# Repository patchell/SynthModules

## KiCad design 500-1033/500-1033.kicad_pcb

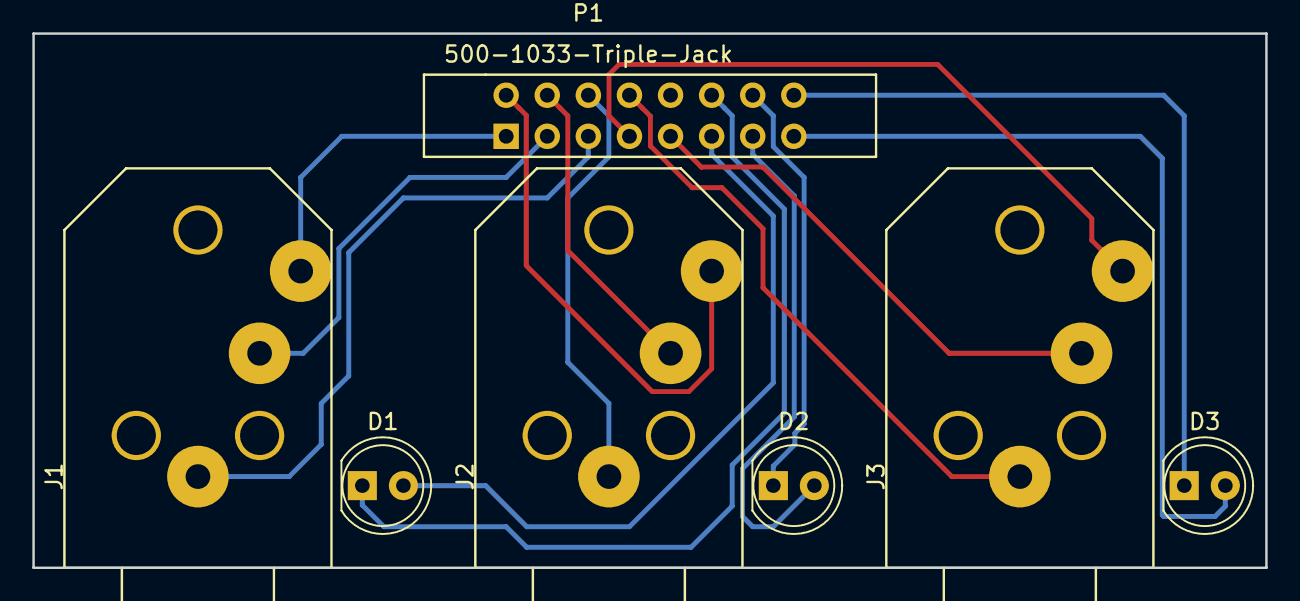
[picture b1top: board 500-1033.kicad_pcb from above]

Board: 2 copper layers, 76.2 x 33.0 mm, 7 parts (0 on the bottom side), 15 nets.

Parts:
D1, D2, D3: LED_ALT; LED_D5.0mm
J1, J2, J3: Phone_Jack_wSw-PCB; PHONE-SC112A
P1: 500-1033-Triple-Jack; IDC8x2_Vert

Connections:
unnamed: D1.1, P1.12
unnamed: D1.2, P1.11
unnamed: D2.1, P1.14
unnamed: D2.2, P1.13
unnamed: D3.1, P1.16
unnamed: D3.2, P1.15
unnamed: J1.1, P1.5
unnamed: J1.2, P1.3
unnamed: J1.3, P1.1
unnamed: J2.1, P1.6
unnamed: J2.2, P1.4
unnamed: J2.3, P1.2
unnamed: J3.1, P1.8
unnamed: J3.2, P1.9
unnamed: J3.3, P1.7

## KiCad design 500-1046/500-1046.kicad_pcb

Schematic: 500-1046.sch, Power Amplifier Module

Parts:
C1: 10uF; Cap-Pol-Rad-0.2_0.1
C2: 100uF; Cap-Pol-Rad-0.2_0.1
C3: 100pF; CAP-GREENIE-0.2
C4, C5, C6, C7: 0.1uF; CAP-GREENIE-0.2
L1: 30uH; AXIAL0.7X0.2
P1: Header_4x1; Header_4Pin_RA_0.1
P2: Header_6x1; TERMINAL-BLOCK-SCREWS
Q1, Q2, Q3, Q6: KSC1845; TO92
Q4, Q5: KSA992; TO92
Q7: MJE340; TO-225
Q8: 2N3904; TO92
Q9: 2N3906; TO92
Q10: TIP142; TO-264
Q11: TIP147; TO-264
R1, R7, R8, R11: 10K; AXIAL0.4
R2, R5: 1.2K; AXIAL0.4
R3, R6: 220; AXIAL0.4
R4: 909; AXIAL0.4
R10, R18: 390; AXIAL0.4
R12, R17, R21, R22: 1K; AXIAL0.4
R13: 15K; AXIAL0.4
R14: 10; AXIAL0.4
R15: 2.2K; AXIAL0.4
R16: 1K; Trimpot-3006
R19, R20: 499; AXIAL0.4
R23, R24: .33; AXIAL0.7X0.2
R25, R26: 10; AXIAL0.7X0.2
U1: LM4041-ADJ; TO92

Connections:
/GND_DIRTY: C4.2, C5.1, P2.2
/GND_H: C6.2, P2.5
/OUT: L1.2, P2.4, R26.2
/V+: C4.1, P2.1, Q10.2, R2.1, R5.1, R12.1, R14.1
/V-: C5.2, P2.6, Q11.2, R4.2, R8.2, R18.2, U1.3 (adj)
GND: C2.2, P1.1, P1.3, P1.4, P2.3, R1.2, R13.1
unnamed: C1.1, Q1.3, R1.1
unnamed: C1.2, P1.2
unnamed: C2.1, R10.2
unnamed: C3.1, Q1.2, Q4.3, R2.2
unnamed: C3.2, C7.1, Q4.2, Q5.2, Q7.2, Q8.3, Q10.1, R15.1
unnamed: C6.1, R25.2
unnamed: C7.2, Q6.2, Q7.1, Q9.3, Q11.1, R17.2
unnamed: L1.1, Q8.1, Q9.1, R11.1, R19.1, R20.2, R23.2, R24.1, R25.1, R26.1
unnamed: Q1.1, R3.1
unnamed: Q2.1, R4.1
unnamed: Q2.2, R3.2, R6.2
unnamed: Q2.3, Q6.3, R7.1, R13.2, U1.2 (cath)
unnamed: Q3.1, R6.1
unnamed: Q3.2, R5.2
unnamed: Q3.3, R10.1, R11.2
unnamed: Q4.1, Q5.3, R12.2
unnamed: Q5.1, R14.2
unnamed: Q6.1, R18.1
unnamed: Q7.3, R16.2
unnamed: Q8.2, R19.2, R21.2
unnamed: Q9.2, R20.1, R22.2
unnamed: Q10.3, R21.1, R23.1
unnamed: Q11.3, R22.1, R24.2
unnamed: R7.2, R8.1, U1.1 (anod)
unnamed: R15.2, R16.1
unnamed: R16.3, R17.1

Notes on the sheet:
L1 Wind 4 Turns of #22 Magnet Wire on an Amidon ft-50-j Torrid Core

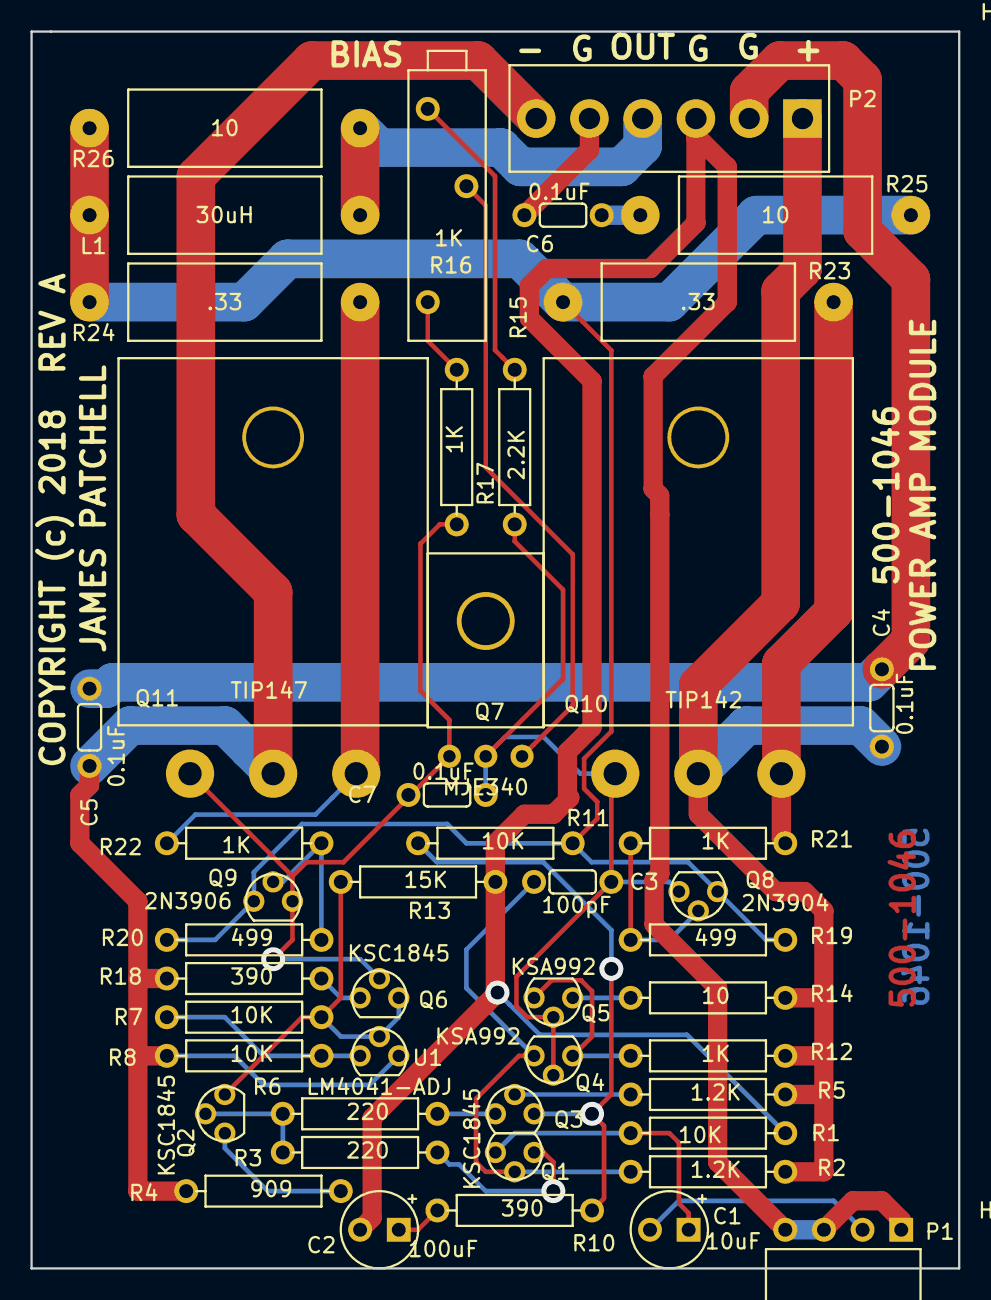
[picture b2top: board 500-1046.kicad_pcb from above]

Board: 2 copper layers, 61.0 x 81.3 mm, 47 parts (0 on the bottom side), 32 nets.

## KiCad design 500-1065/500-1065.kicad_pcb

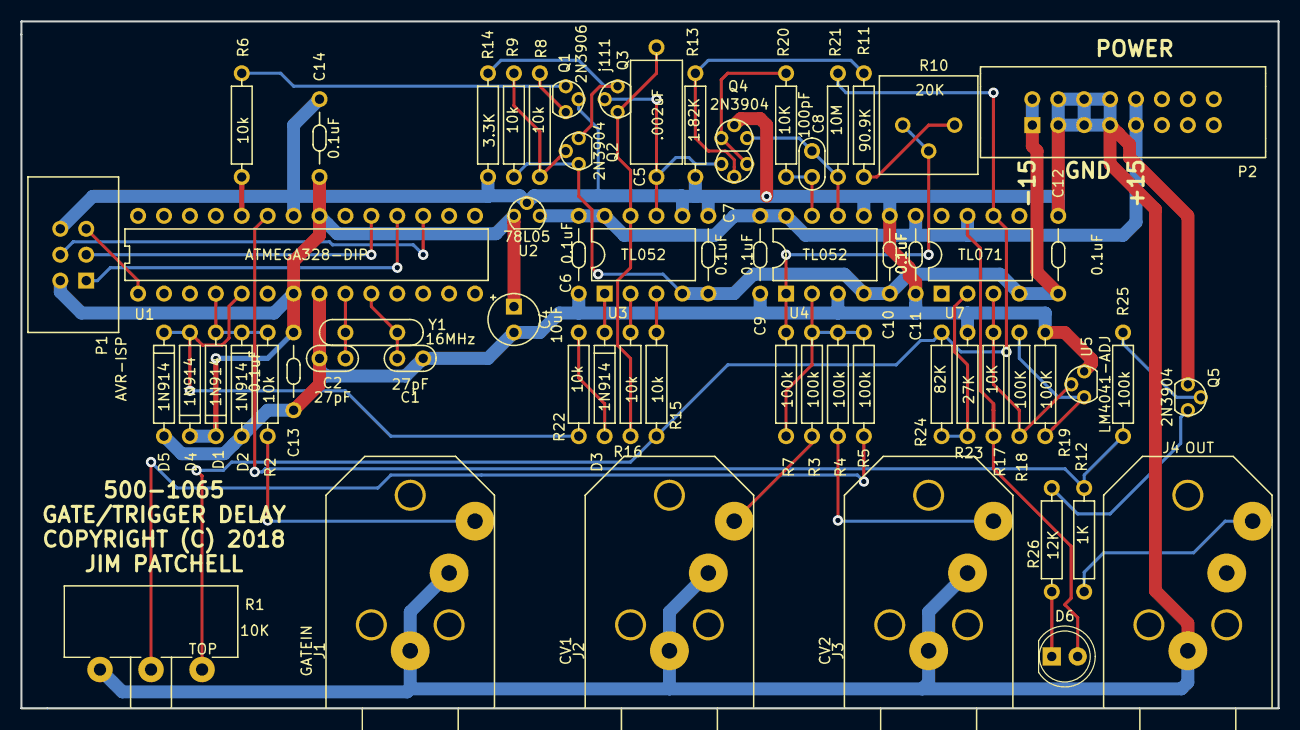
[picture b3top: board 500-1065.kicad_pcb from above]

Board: 2 copper layers, 123.2 x 67.3 mm, 63 parts (0 on the bottom side), 43 nets.

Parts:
C1, C2: 27pF; CAP-0.1
C4: 10uF; Cap-Pol-Rad-0.2_0.1
C5: .002uF; CAP-AXIAL-0.5x0.2
C6, C7, C9, C10, C11, C12, C13, C14: 0.1uF; CAP-Bypass-0_3
C8: 100pF; CAP-0.1
D1, D2, D3, D4, D5: 1N914; DIODE0.4
D6: LED_ALT; LED_5.0mm
J1: GATEIN; PHONE-SC112A
J2: CV1; PHONE-SC112A
J3: CV2; PHONE-SC112A
J4: OUT; PHONE-SC112A
P1: AVR-ISP; IDC3X2
P2: EurorackPower16pin; IDC8x2_Vert
Q1: 2N3906; TO92
Q2, Q5: 2N3904; TO92
Q3: j111; TO92
Q4: 2N3904; DUAL_TO92
R1: 10K; Alpha-Pot-16mm-RA-PCB
R2, R6, R8, R9, R15, R16, R22: 10k; AXIAL0_4
R3, R4, R5, R7, R25: 100k; AXIAL0_4
R10: 20K; Trimpot
R11: 90.9K; AXIAL0_4
R12: 1K; AXIAL0_4
R13: 1.82K; AXIAL0_4
R14: 3.3K; AXIAL0_4
R17, R20: 10K; AXIAL0_4
R18, R19: 100K; AXIAL0_4
R21: 10M; AXIAL0_4
R23: 27K; AXIAL0_4
R24: 82K; AXIAL0_4
R26: 12K; AXIAL0_4
U1: ATMEGA328-DIP; DIP28.3
U2: 78L05; TO92
U3, U4: TL052; DIP8
U5: LM4041-ADJ; TO92
U7: TL071; DIP8
Y1: 16MHz; XTAL

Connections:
+15V0: C6.1, C9.1, C11.1, D6.2, P2.9, P2.10, R17.2, U2.3, U3.8, U4.8, U7.7
-15V0: C7.1, C10.1, C12.1, P2.1, P2.2, Q2.1, R9.2, U3.4, U4.4, U7.4
/OUT: R12.1, R25.1, U1.23
GND: C1.2, C2.2, C4.2, C6.2, C7.2, C9.2, C10.2, C11.2, C12.2, C13.2, C14.2, D2.2, D5.2, J1.1, J1.2, J2.1, J2.2, J3.1, J3.2, J4.1, P1.6, P2.3, P2.4, P2.5, P2.6, P2.7, P2.8, Q1.2, Q4.5, Q5.1, R1.3, R13.2, R14.1, R19.2, R23.2, U1.8, U1.22, U2.2, U3.5, U4.3, U4.5, U5.3
unnamed: C1.1, U1.10, Y1.1
unnamed: C2.1, U1.9, Y1.2
unnamed: C5.1, Q3.2, Q4.3, U3.6
unnamed: C5.2, Q3.1, R16.1, U3.7
unnamed: C8.1, Q4.6, R21.2, U4.6
unnamed: C8.2, R20.2, U4.7
unnamed: D1.2, D2.1, R2.2, U1.4
unnamed: D3.1, U3.1
unnamed: D3.2, R22.1
unnamed: D4.2, D5.1, R22.2, U1.5
unnamed: D6.1, R26.1
unnamed: J1.3, R2.1
unnamed: J2.3, R3.1
unnamed: J3.3, R4.1
unnamed: J4.3, R12.2
unnamed: P1.1, U1.18
unnamed: P1.3, U1.19
unnamed: P1.4, U1.17
unnamed: P1.5, U1.1
unnamed: Q1.1, R6.2
unnamed: Q1.3, R8.1
unnamed: Q2.2, R8.2, R9.1
unnamed: Q2.3, Q3.3, R14.2
unnamed: Q4.1, Q4.4, R20.1
unnamed: Q4.2, R11.2, R13.1
unnamed: Q5.2, R25.2
unnamed: Q5.3, R26.2
unnamed: R1.1, R15.1, R21.1, R24.1, U7.6
unnamed: R1.2, R5.1
unnamed: R3.2, R4.2, R5.2, R7.1, U4.2
unnamed: R6.1, U1.24
unnamed: R7.2, R10.1, R10.2, U4.1
unnamed: R10.3, R11.1
unnamed: R15.2, U3.3
unnamed: R16.2, U3.2
unnamed: R17.1, R18.1, U5.2, U7.3
unnamed: R18.2, R19.1, U5.1
unnamed: R23.1, R24.2, U7.2
VCC: C4.1, C13.1, C14.1, D1.1, D4.1, P1.2, U1.7, U1.21, U2.1

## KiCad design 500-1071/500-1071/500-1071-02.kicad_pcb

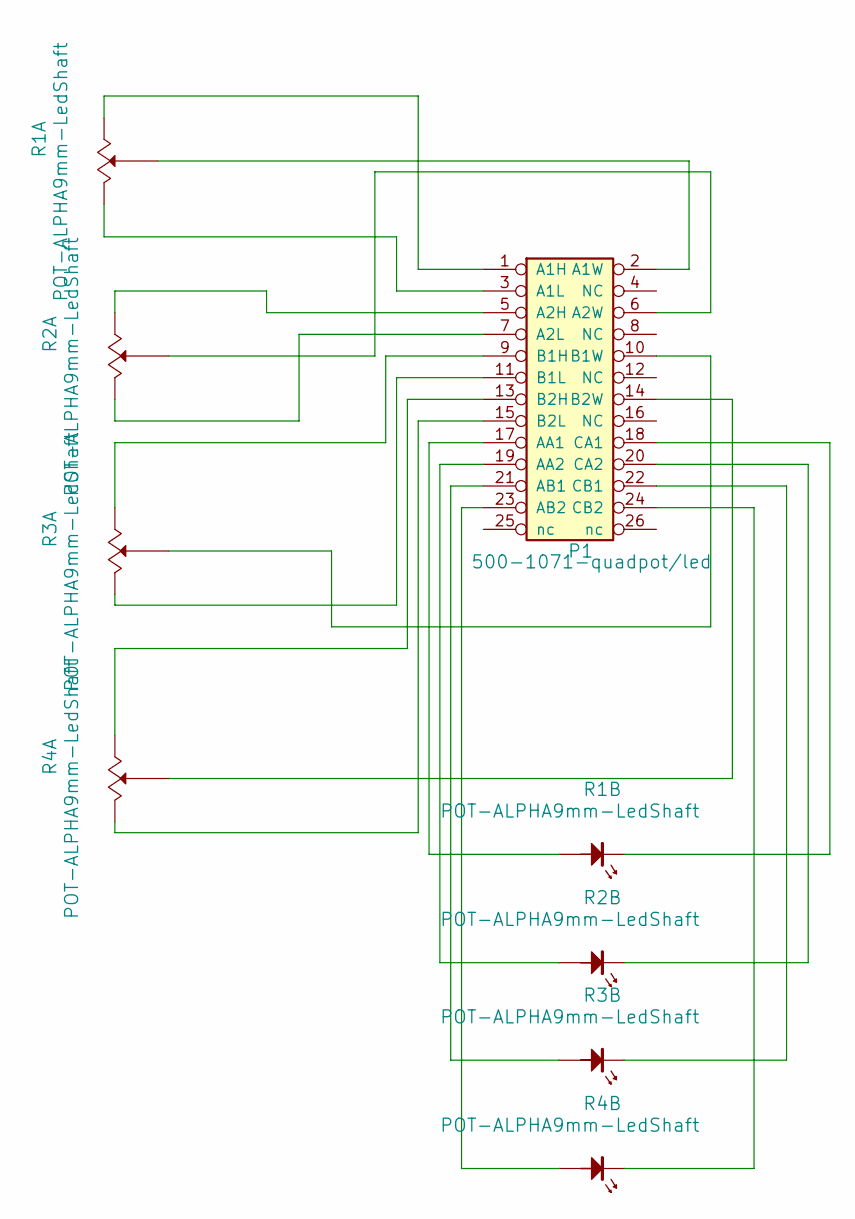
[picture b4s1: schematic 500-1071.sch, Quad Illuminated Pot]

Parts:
P1: 500-1071-quadpot/led; IDC-13x2
R1, R2, R3, R4: POT-ALPHA9mm-LedShaft; Alpha9mmPotWithLED

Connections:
unnamed: P1.1 (A1H), R1.1 (A)
unnamed: P1.2 (A1W), R1.2 (Wiper)
unnamed: P1.3 (A1L), R1.3 (B)
unnamed: P1.5 (A2H), R2.1 (A)
unnamed: P1.6 (A2W), R2.2 (Wiper)
unnamed: P1.7 (A2L), R2.3 (B)
unnamed: P1.9 (B1H), R3.1 (A)
unnamed: P1.10 (B1W), R3.2 (Wiper)
unnamed: P1.11 (B1L), R3.3 (B)
unnamed: P1.13 (B2H), R4.1 (A)
unnamed: P1.14 (B2W), R4.2 (Wiper)
unnamed: P1.15 (B2L), R4.3 (B)
unnamed: P1.17 (AA1), R1.5 (ANODE)
unnamed: P1.18 (CA1), R1.4 (CATHODE)
unnamed: P1.19 (AA2), R2.5 (ANODE)
unnamed: P1.20 (CA2), R2.4 (CATHODE)
unnamed: P1.21 (AB1), R3.5 (ANODE)
unnamed: P1.22 (CB1), R3.4 (CATHODE)
unnamed: P1.23 (AB2), R4.5 (ANODE)
unnamed: P1.24 (CB2), R4.4 (CATHODE)

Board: 2 copper layers, 5 parts (4 on the bottom side), 20 nets, no tracks yet.

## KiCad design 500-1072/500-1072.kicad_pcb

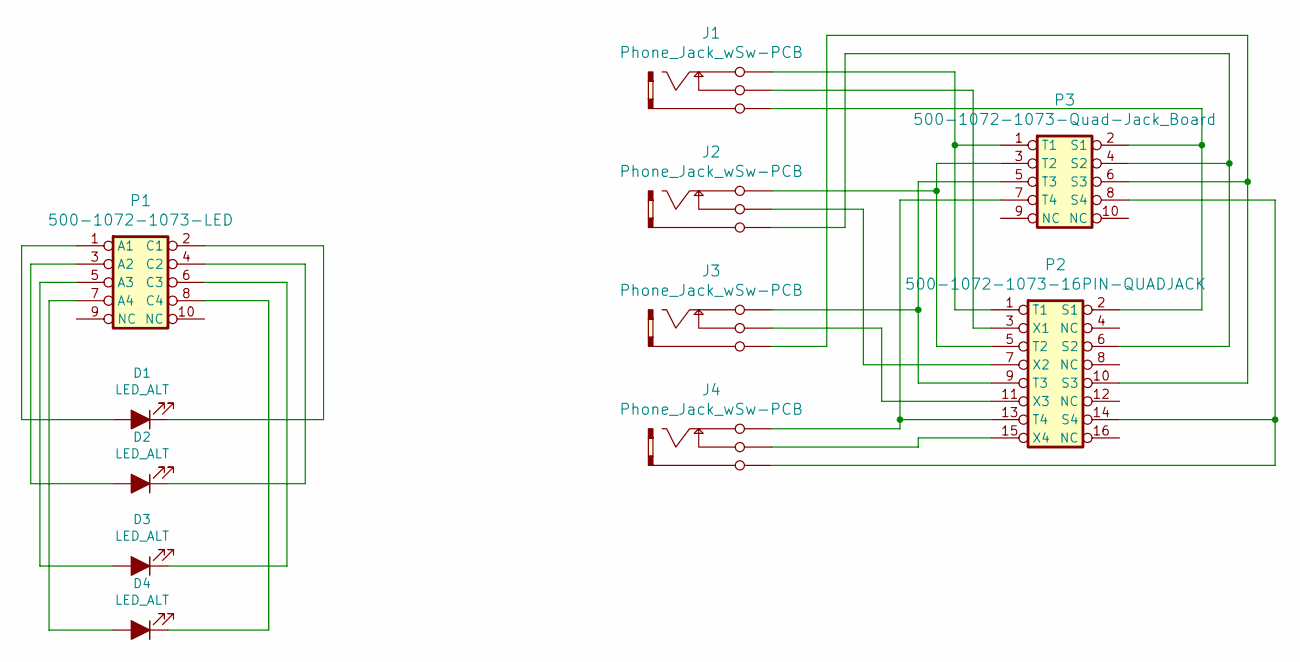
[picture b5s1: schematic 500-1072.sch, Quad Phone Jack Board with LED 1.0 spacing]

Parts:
D1, D2, D3, D4: LED_ALT; LED_5.0mm
J1, J2, J3, J4: Phone_Jack_wSw-PCB; PHONE-SC112A
P1: 500-1072-1073-LED; IDC5x2_Vert
P2: 500-1072-1073-16PIN-QUADJACK; IDC8x2_Vert
P3: 500-1072-1073-Quad-Jack_Board; IDC5x2_Vert

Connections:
unnamed: D1.1 (K), P1.2 (C1)
unnamed: D1.2 (A), P1.1 (A1)
unnamed: D2.1 (K), P1.4 (C2)
unnamed: D2.2 (A), P1.3 (A2)
unnamed: D3.1 (K), P1.6 (C3)
unnamed: D3.2 (A), P1.5 (A3)
unnamed: D4.1 (K), P1.8 (C4)
unnamed: D4.2 (A), P1.7 (A4)
unnamed: J1.1 (Gnd), P2.2 (S1), P3.2 (S1)
unnamed: J1.2 (Sw), P2.3 (X1)
unnamed: J1.3 (Tip), P2.1 (T1), P3.1 (T1)
unnamed: J2.1 (Gnd), P2.6 (S2), P3.4 (S2)
unnamed: J2.2 (Sw), P2.7 (X2)
unnamed: J2.3 (Tip), P2.5 (T2), P3.3 (T2)
unnamed: J3.1 (Gnd), P2.10 (S3), P3.6 (S3)
unnamed: J3.2 (Sw), P2.11 (X3)
unnamed: J3.3 (Tip), P2.9 (T3), P3.5 (T3)
unnamed: J4.1 (Gnd), P2.14 (S4), P3.8 (S4)
unnamed: J4.2 (Sw), P2.15 (X4)
unnamed: J4.3 (Tip), P2.13 (T4), P3.7 (T4)

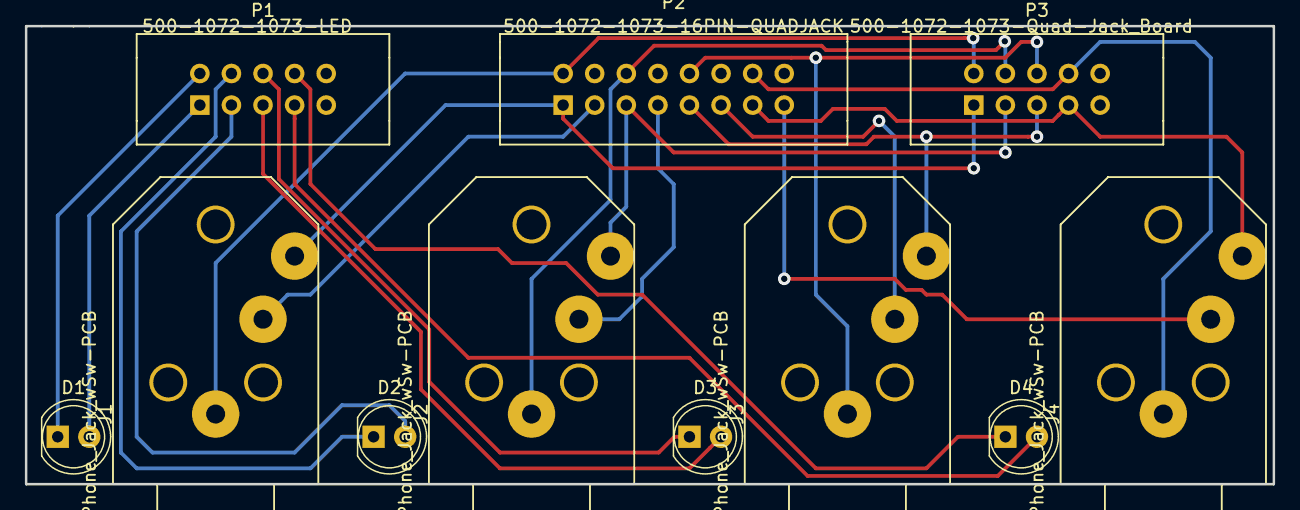
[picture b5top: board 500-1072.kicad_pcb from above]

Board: 2 copper layers, 100.3 x 36.8 mm, 11 parts (0 on the bottom side), 20 nets.

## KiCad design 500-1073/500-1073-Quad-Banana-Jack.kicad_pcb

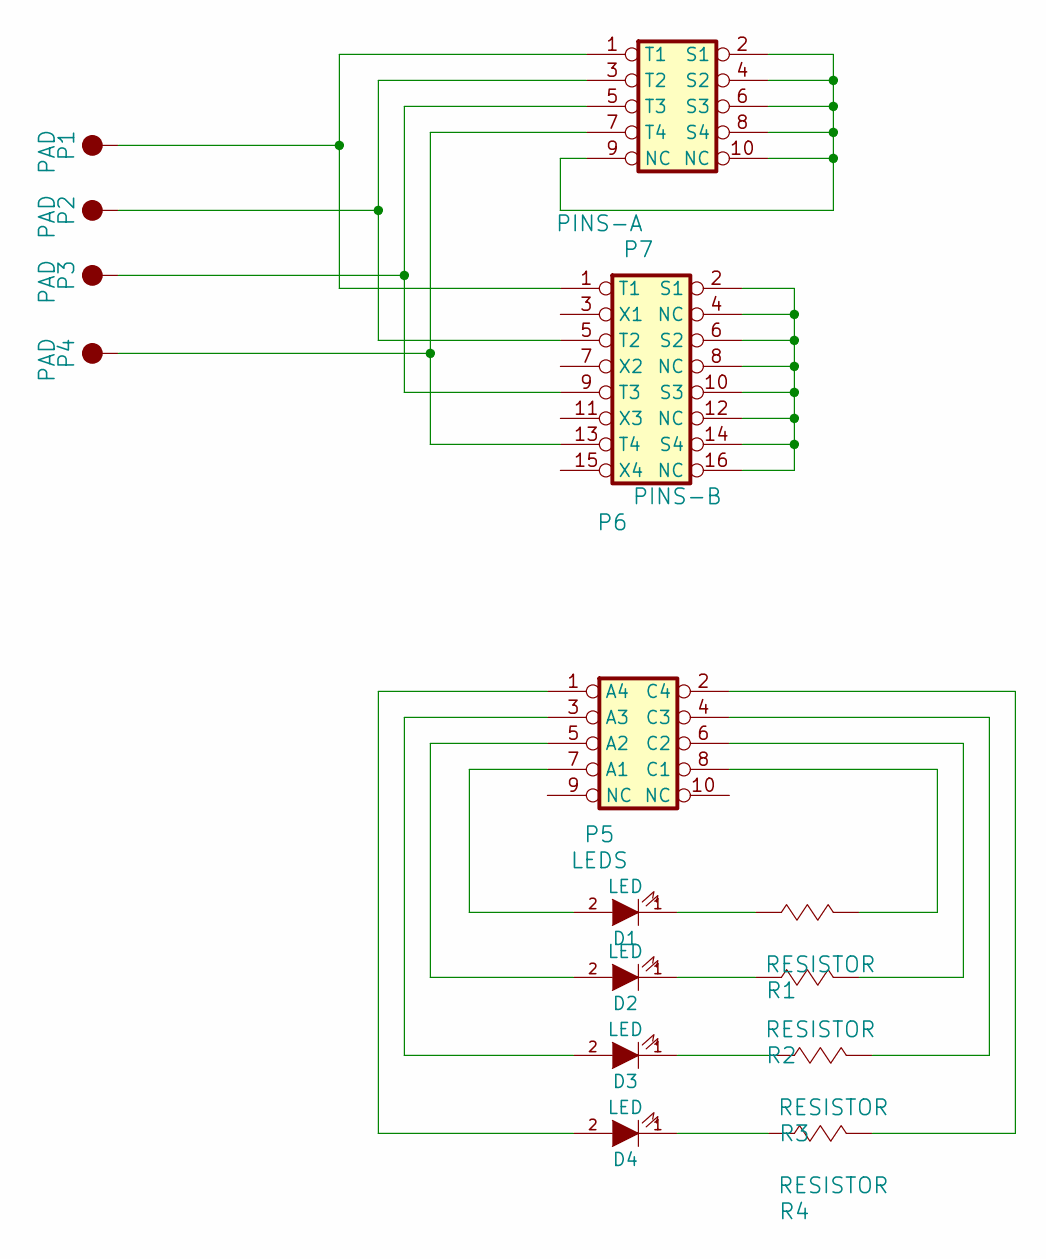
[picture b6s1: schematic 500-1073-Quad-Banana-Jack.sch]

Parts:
D1, D2, D3, D4: LED; LED-5MM
P1, P2, P3, P4: PAD; KF2-256-TerminalPad
P5: LEDS; IDC5x2_Vert
P6: PINS-B; IDC8x2_Vert
P7: PINS-A; IDC5x2_Vert
R1, R2, R3, R4: RESISTOR; AXIAL0.4

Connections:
unnamed: D1.1 (K), R1.1 (A)
unnamed: D1.2 (A), P5.7 (A1)
unnamed: D2.1 (K), R2.1 (A)
unnamed: D2.2 (A), P5.5 (A2)
unnamed: D3.1 (K), R3.1 (A)
unnamed: D3.2 (A), P5.3 (A3)
unnamed: D4.1 (K), R4.1 (A)
unnamed: D4.2 (A), P5.1 (A4)
unnamed: P1.1, P6.1 (T1), P7.1 (T1)
unnamed: P2.1, P6.5 (T2), P7.3 (T2)
unnamed: P3.1, P6.9 (T3), P7.5 (T3)
unnamed: P4.1, P6.13 (T4), P7.7 (T4)
unnamed: P5.2 (C4), R4.2 (B)
unnamed: P5.4 (C3), R3.2 (B)
unnamed: P5.6 (C2), R2.2 (B)
unnamed: P5.8 (C1), R1.2 (B)
unnamed: P6.2 (S1), P6.4 (NC), P6.6 (S2), P6.8 (NC), P6.10 (S3), P6.12 (NC), P6.14 (S4), P6.16 (NC)
unnamed: P7.2 (S1), P7.4 (S2), P7.6 (S3), P7.8 (S4), P7.9 (NC), P7.10 (NC)

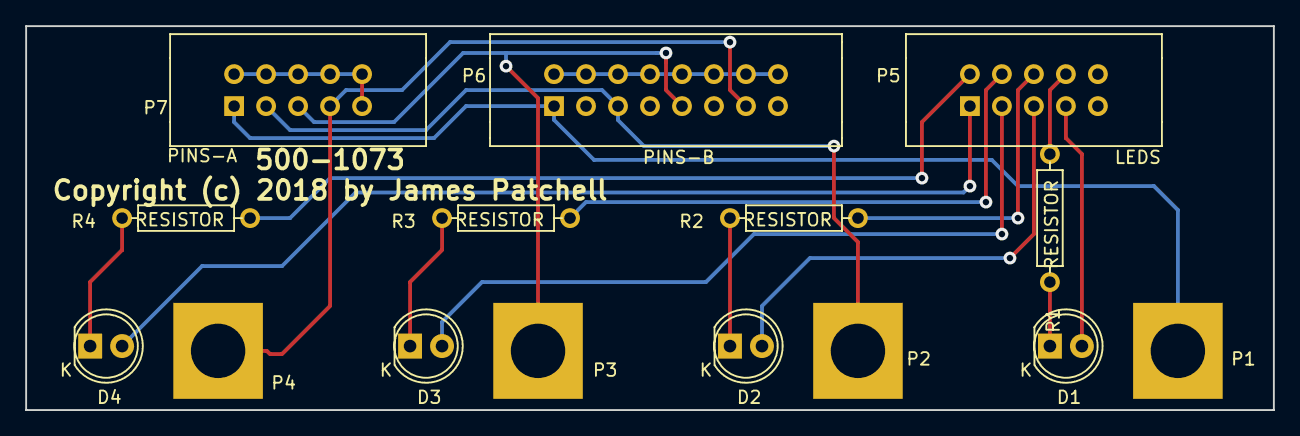
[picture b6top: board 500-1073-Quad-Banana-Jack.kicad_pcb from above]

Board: 2 copper layers, 99.1 x 30.5 mm, 15 parts (0 on the bottom side), 18 nets.

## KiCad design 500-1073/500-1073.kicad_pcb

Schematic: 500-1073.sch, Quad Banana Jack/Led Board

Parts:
D1, D2, D3, D4: LED_ALT; LED_D5.0mm
P1: 500-1072-1073-Quad-Jack_Board; IDC5x2_Vert
P2, P3, P5, P6: PAD-KF2-256; KF2-256-TerminalPad
P4: 500-1072-1073-16PIN-QUADJACK; IDC8x2_Vert
P7: 500-1072-1073-LED; IDC5x2_Vert

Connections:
unnamed: D1.1, P7.2 (C4)
unnamed: D1.2, P7.1 (A4)
unnamed: D2.1, P7.4 (C3)
unnamed: D2.2, P7.3 (A3)
unnamed: D3.1, P7.6 (C2)
unnamed: D3.2, P7.5 (A2)
unnamed: D4.1, P7.8 (C1)
unnamed: D4.2, P7.7 (A1)
unnamed: P1.1 (T1), P2.1, P4.1 (T1)
unnamed: P1.3 (T2), P3.1, P4.5 (T2)
unnamed: P1.5 (T3), P4.9 (T3), P5.1
unnamed: P1.7 (T4), P4.13 (T4), P6.1

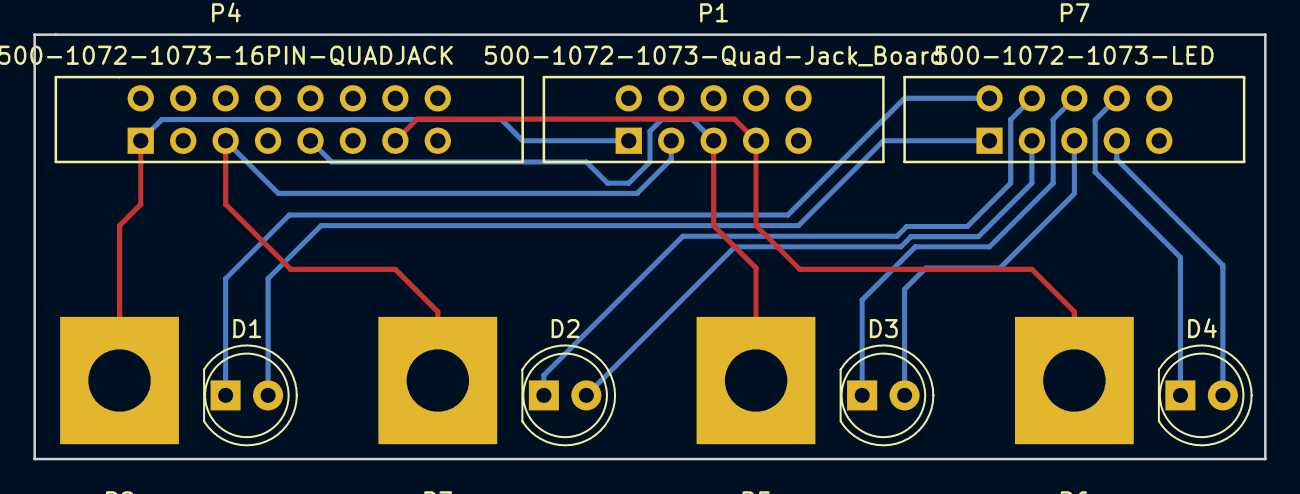
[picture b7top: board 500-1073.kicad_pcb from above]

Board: 2 copper layers, 73.7 x 25.4 mm, 11 parts (0 on the bottom side), 12 nets.

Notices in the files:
500-1046/500-1046.kicad_pcb:
COPYRIGHT (c) 2018  REV A
500-1073/500-1073-Quad-Banana-Jack.kicad_pcb:
Copyright (c) 2018 by James Patchell
